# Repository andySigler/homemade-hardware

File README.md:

# Homemade Hardware

This repository holds supporting materials for the NYU-ITP graduate course [Homemade Hardware](http://www.homemadehardware.com)

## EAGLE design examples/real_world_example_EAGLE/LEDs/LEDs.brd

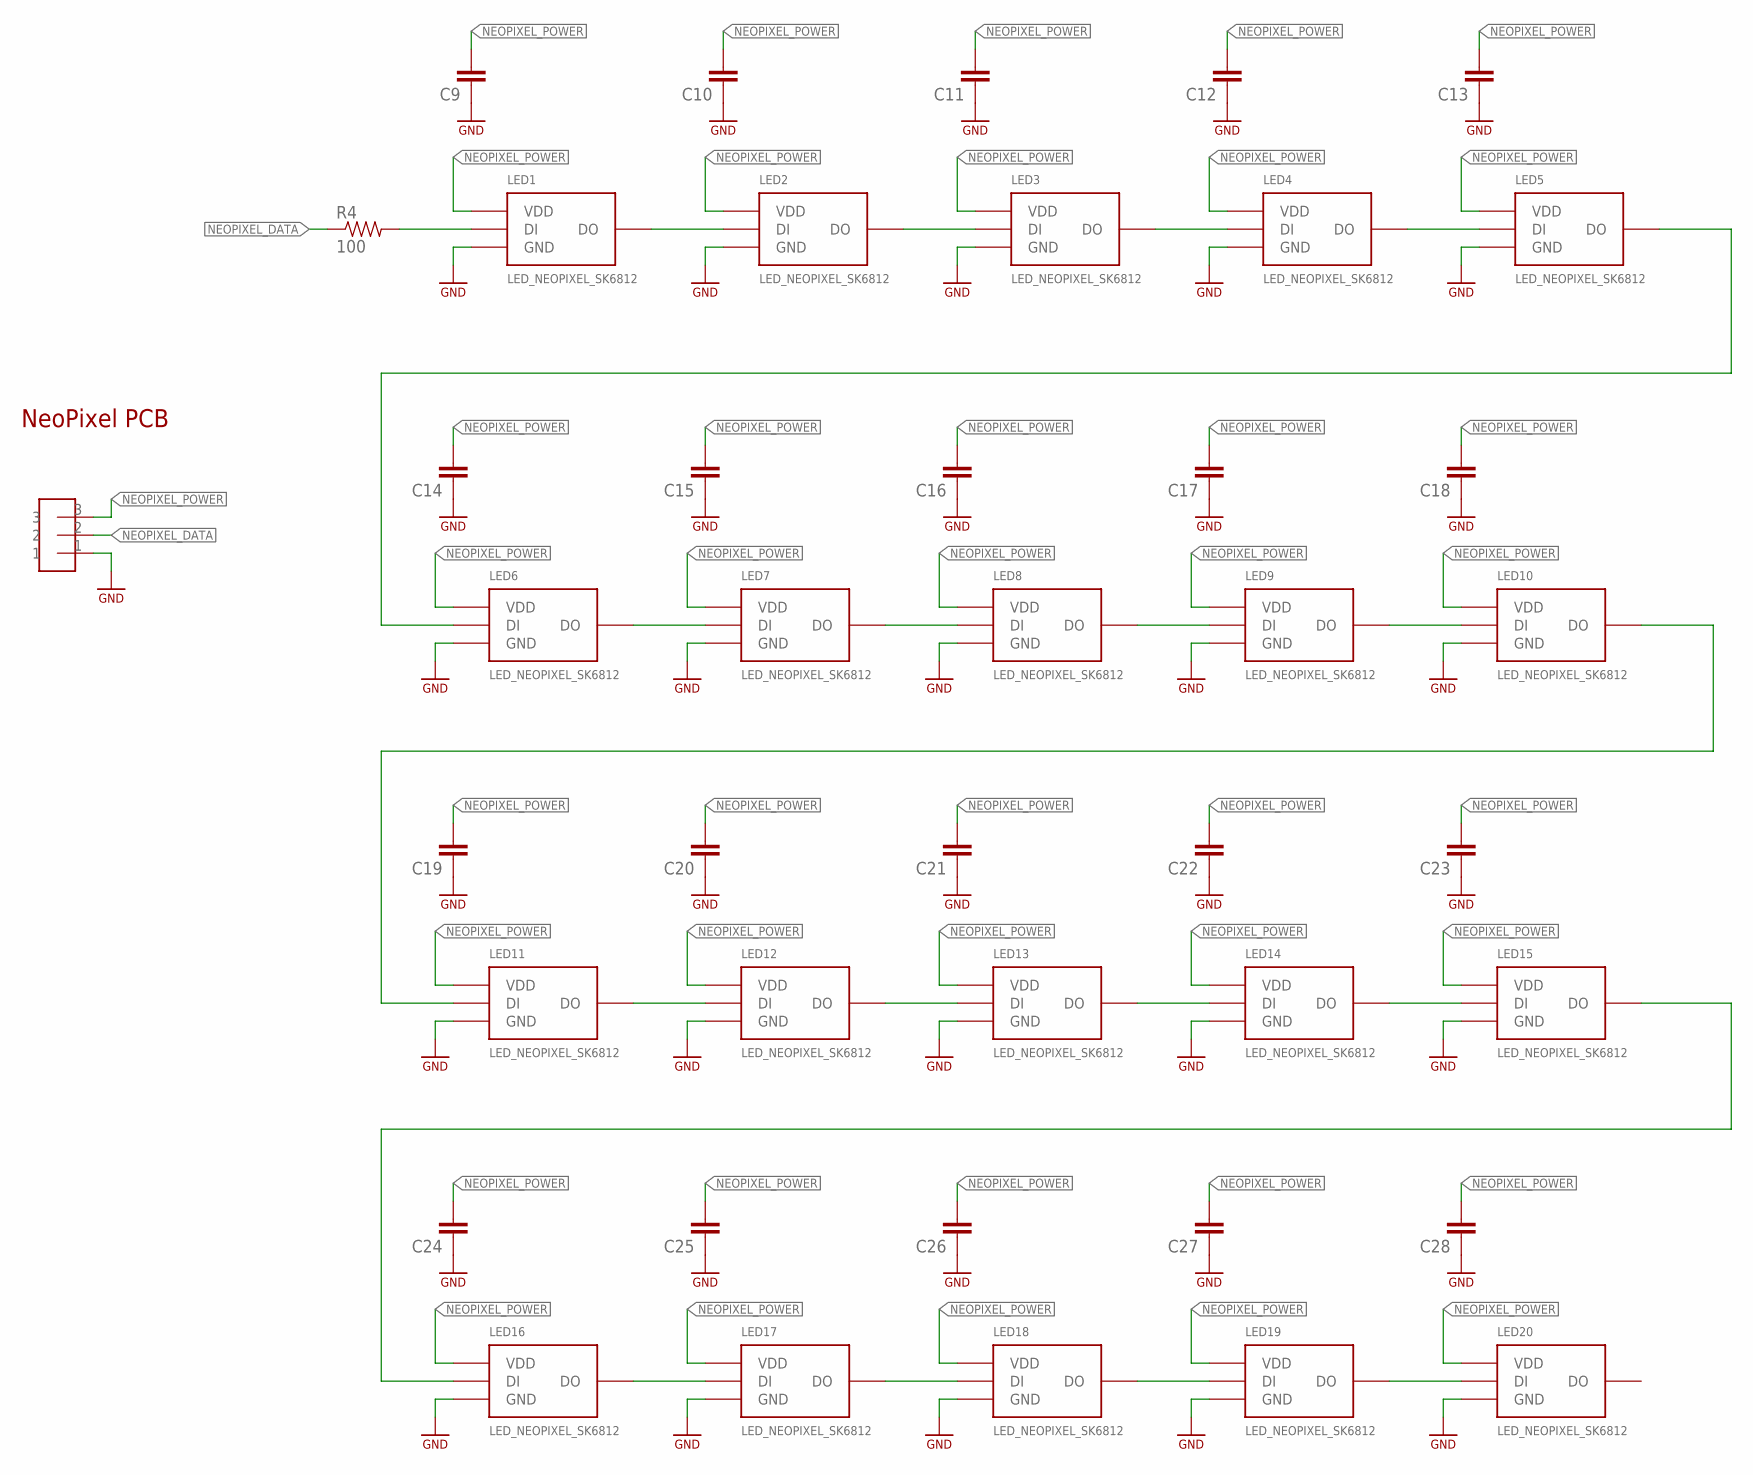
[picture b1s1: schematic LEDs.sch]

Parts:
C9, C10, C11, C12, C13, C14, C15, C16, C17, C18, C19, C20, C21, C22, C23, C24, C25, C26, C27, C28: COMPONENT_CAP-0805; 0805
LED1, LED2, LED3, LED4, LED5, LED6, LED7, LED8, LED9, LED10, LED11, LED12, LED13, LED14, LED15, LED16, LED17, LED18, LED19, LED20: LED_NEOPIXEL_SK6812; SK6812
R4: 100; 0805
U$2: HEADER-3-HORIZONTAL

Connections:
GND: C9.1, C10.1, C11.1, C12.1, C13.1, C14.1, C15.1, C16.1, C17.1, C18.1, C19.1, C20.1, C21.1, C22.1, C23.1, C24.1, C25.1, C26.1, C27.1, C28.1, LED1.3-GND (GND), LED2.3-GND (GND), LED3.3-GND (GND), LED4.3-GND (GND), LED5.3-GND (GND), LED6.3-GND (GND), LED7.3-GND (GND), LED8.3-GND (GND), LED9.3-GND (GND), LED10.3-GND (GND), LED11.3-GND (GND), LED12.3-GND (GND), LED13.3-GND (GND), LED14.3-GND (GND), LED15.3-GND (GND), LED16.3-GND (GND), LED17.3-GND (GND), LED18.3-GND (GND), LED19.3-GND (GND), LED20.3-GND (GND), U$2.1
unnamed: LED1.4-DIN (DI), R4.2
unnamed: LED1.2-DOUT (DO), LED2.4-DIN (DI)
unnamed: LED2.2-DOUT (DO), LED3.4-DIN (DI)
unnamed: LED3.2-DOUT (DO), LED4.4-DIN (DI)
unnamed: LED4.2-DOUT (DO), LED5.4-DIN (DI)
unnamed: LED5.2-DOUT (DO), LED6.4-DIN (DI)
unnamed: LED6.2-DOUT (DO), LED7.4-DIN (DI)
unnamed: LED7.2-DOUT (DO), LED8.4-DIN (DI)
unnamed: LED8.2-DOUT (DO), LED9.4-DIN (DI)
unnamed: LED9.2-DOUT (DO), LED10.4-DIN (DI)
unnamed: LED10.2-DOUT (DO), LED11.4-DIN (DI)
unnamed: LED11.2-DOUT (DO), LED12.4-DIN (DI)
unnamed: LED12.2-DOUT (DO), LED13.4-DIN (DI)
unnamed: LED13.2-DOUT (DO), LED14.4-DIN (DI)
unnamed: LED14.2-DOUT (DO), LED15.4-DIN (DI)
unnamed: LED15.2-DOUT (DO), LED16.4-DIN (DI)
unnamed: LED16.2-DOUT (DO), LED17.4-DIN (DI)
unnamed: LED17.2-DOUT (DO), LED18.4-DIN (DI)
unnamed: LED18.2-DOUT (DO), LED19.4-DIN (DI)
unnamed: LED19.2-DOUT (DO), LED20.4-DIN (DI)
NEOPIXEL_DATA: R4.1, U$2.2
NEOPIXEL_POWER: C9.2, C10.2, C11.2, C12.2, C13.2, C14.2, C15.2, C16.2, C17.2, C18.2, C19.2, C20.2, C21.2, C22.2, C23.2, C24.2, C25.2, C26.2, C27.2, C28.2, LED1.1-VDD (VDD), LED2.1-VDD (VDD), LED3.1-VDD (VDD), LED4.1-VDD (VDD), LED5.1-VDD (VDD), LED6.1-VDD (VDD), LED7.1-VDD (VDD), LED8.1-VDD (VDD), LED9.1-VDD (VDD), LED10.1-VDD (VDD), LED11.1-VDD (VDD), LED12.1-VDD (VDD), LED13.1-VDD (VDD), LED14.1-VDD (VDD), LED15.1-VDD (VDD), LED16.1-VDD (VDD), LED17.1-VDD (VDD), LED18.1-VDD (VDD), LED19.1-VDD (VDD), LED20.1-VDD (VDD), U$2.3

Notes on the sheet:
NeoPixel PCB

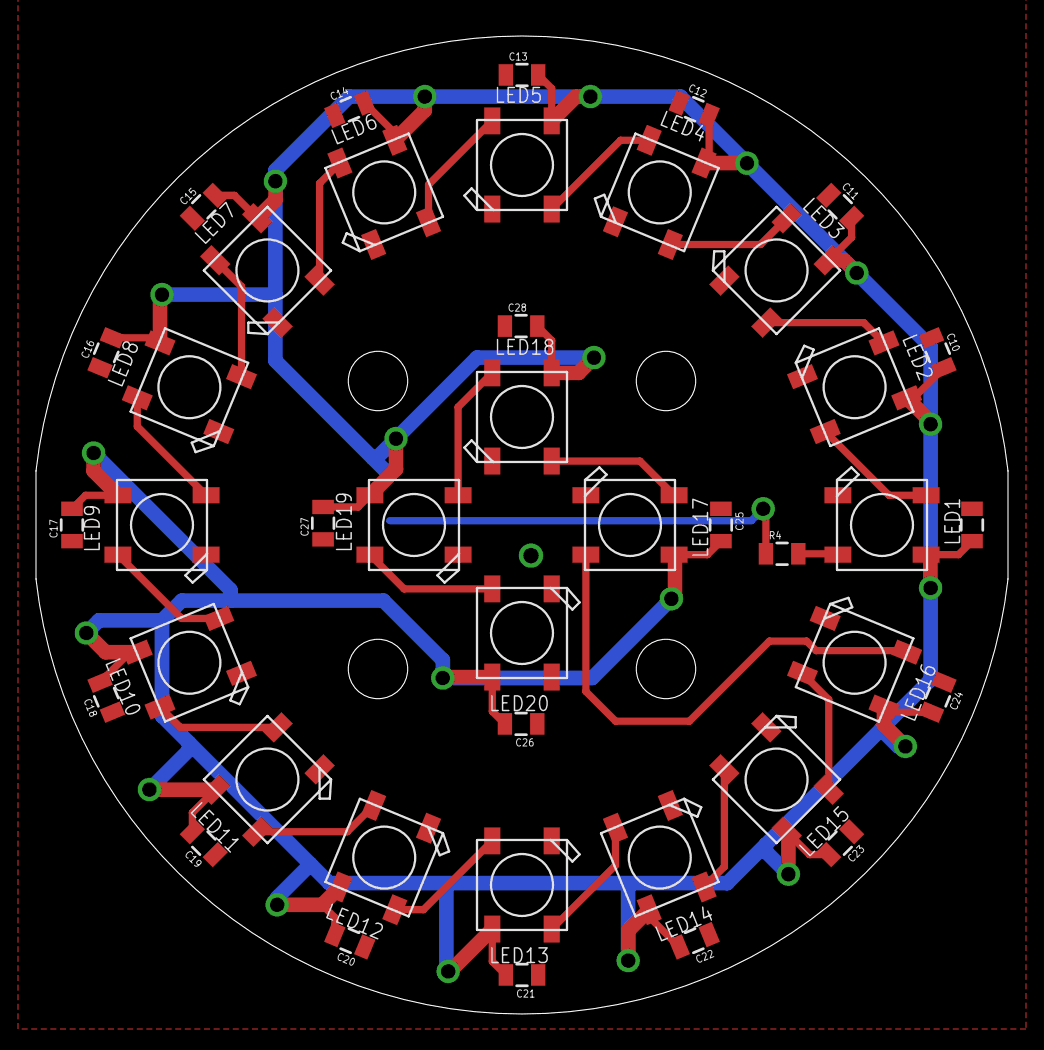
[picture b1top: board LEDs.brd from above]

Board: 2 copper layers, 54.0 x 54.3 mm, 42 parts (1 on the bottom side), 23 nets.

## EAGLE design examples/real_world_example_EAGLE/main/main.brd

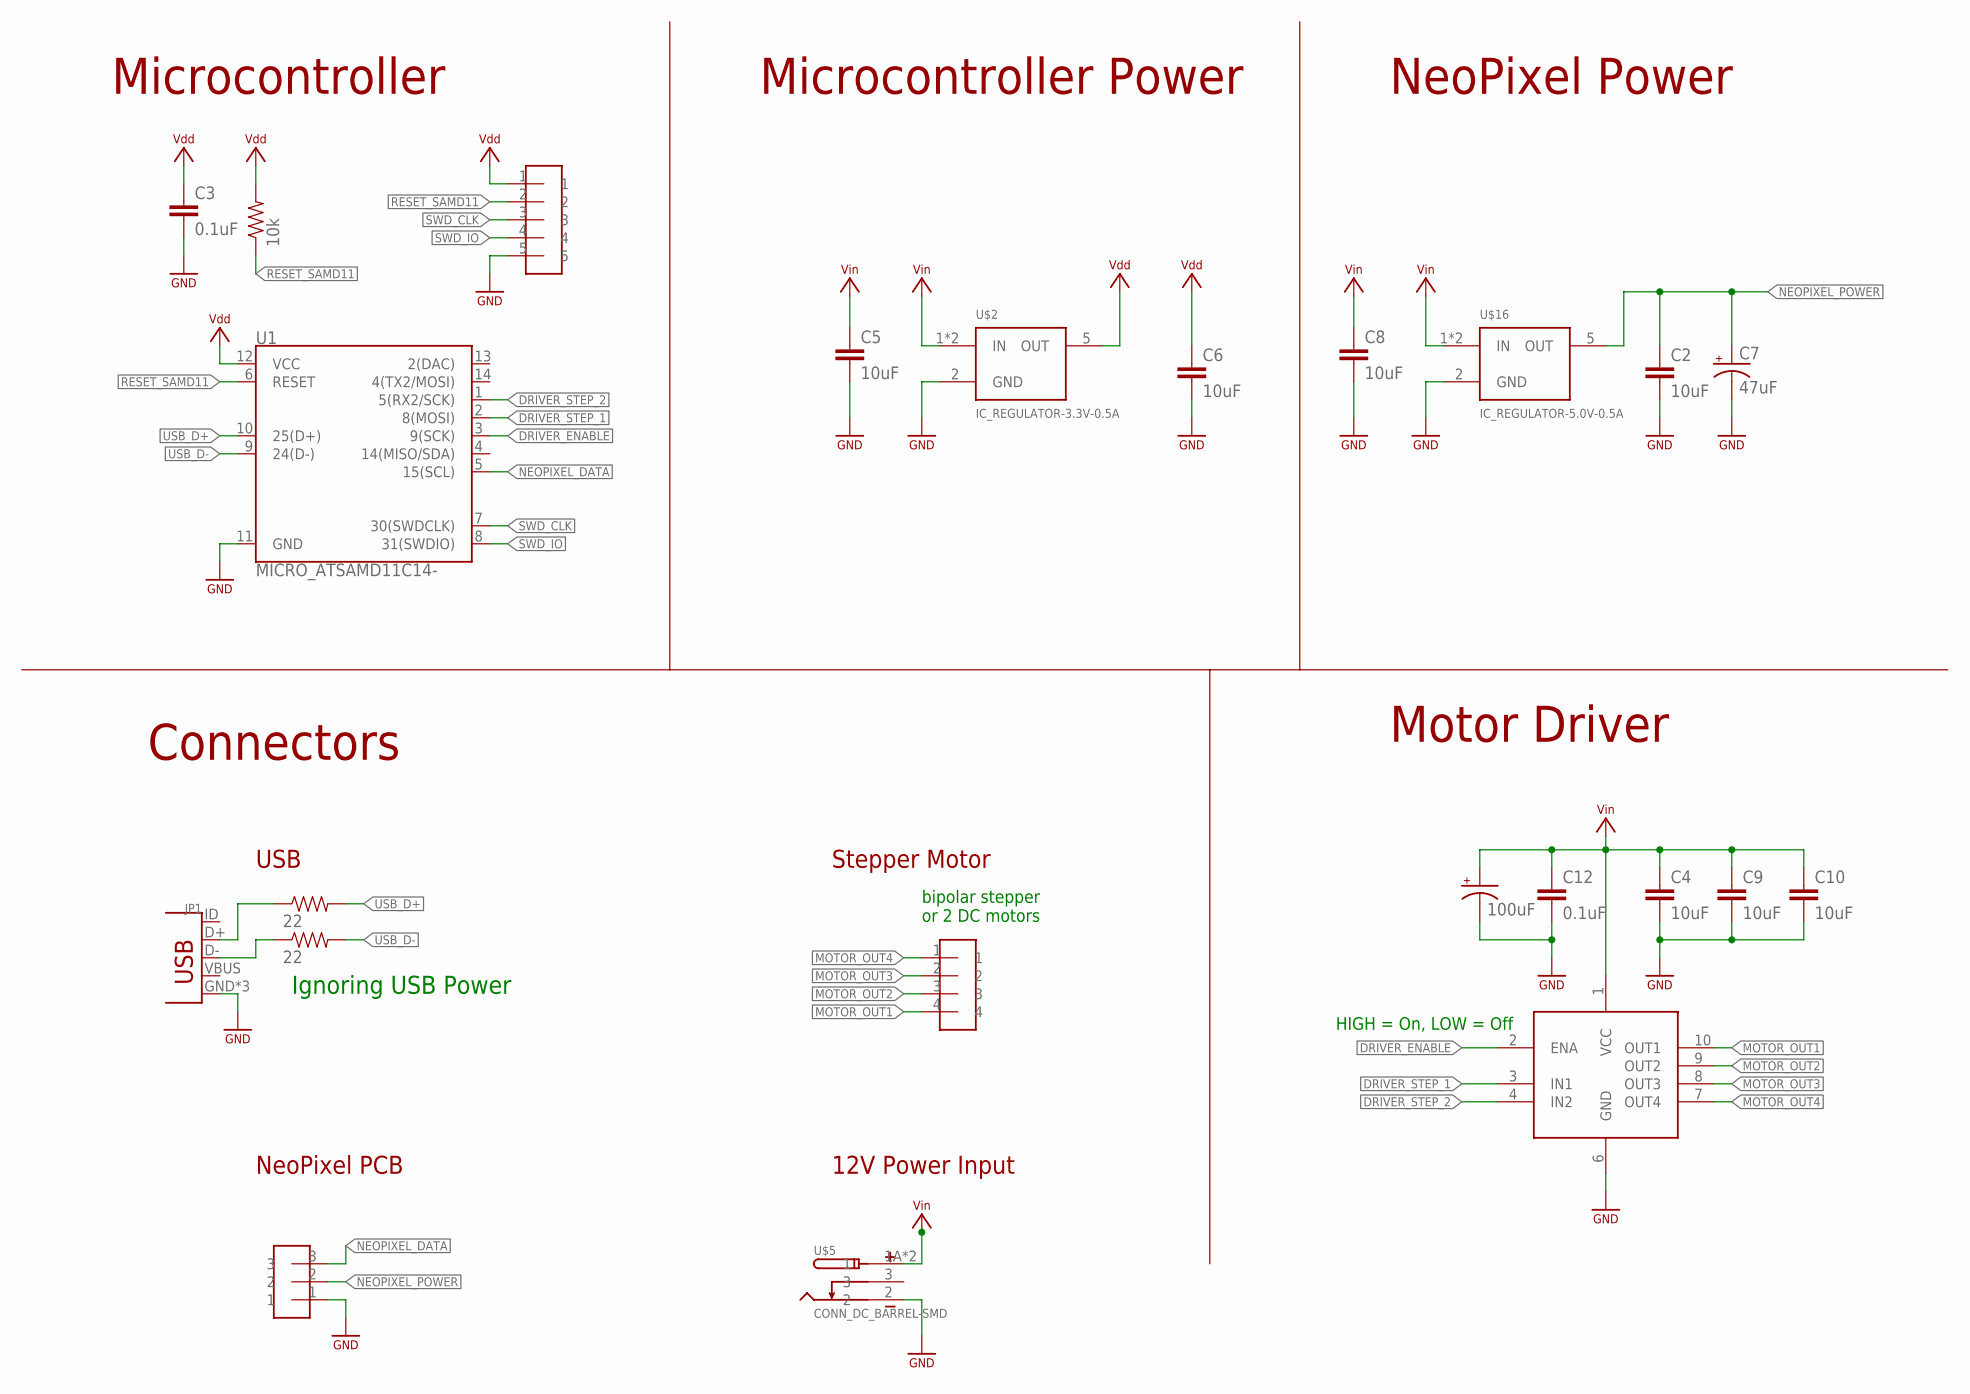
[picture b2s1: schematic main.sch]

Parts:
C1: 100uF; CAP_RADIAL_CAN_8MM
C2, C4, C5, C6, C8, C9, C10: 10uF; 0805
C3, C12: 0.1uF; 0805
C7: 47uF; CAP_RADIAL_CAN_6.3MM
JP1: CONN_USB-10118192-0001LF; USB-MICRO-FEMALE
R1: 10k; 0805
R2, R3: 22; 0805
U1: MICRO_ATSAMD11C14-; SOIC14
U$1: HEADER-4-HORIZONTAL
U$2: IC_REGULATOR-3.3V-0.5A; SOT23-5
U$3: IC_H_BRIDGE_LV8549MC; SOIC10
U$5: CONN_DC_BARREL-SMD; 694106106102
U$10: HEADER-5-TESTPOINT; TESTPOINT-5
U$16: IC_REGULATOR-5.0V-0.5A; SOT23-5
U$17: HEADER-3-HORIZONTAL

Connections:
DRIVER_ENABLE: U1.3 (9(SCK)), U$3.2 (ENA)
DRIVER_STEP_1: U1.2 (8(MOSI)), U$3.3 (IN1)
DRIVER_STEP_2: U1.1 (5(RX2/SCK)), U$3.4 (IN2)
GND: C1.-, C2.2, C3.2, C4.2, C5.2, C6.2, C7.-, C8.2, C9.2, C10.2, C12.2, JP1.GND, JP1.MT1 (GND), JP1.MT2 (GND), U1.11 (GND), U$2.2 (GND), U$3.6 (GND), U$5.2, U$10.5, U$16.2 (GND), U$17.1
MOTOR_OUT1: U$1.4, U$3.10 (OUT1)
MOTOR_OUT2: U$1.3, U$3.9 (OUT2)
MOTOR_OUT3: U$1.2, U$3.8 (OUT3)
MOTOR_OUT4: U$1.1, U$3.7 (OUT4)
unnamed: JP1.D+, R2.1
unnamed: JP1.D-, R3.1
NEOPIXEL_DATA: U1.5 (15(SCL)), U$17.3
NEOPIXEL_POWER: C2.1, C7.+, U$16.5 (OUT), U$17.2
RESET_SAMD11: R1.1, U1.6 (RESET), U$10.2
SWD_CLK: U1.7 (30(SWDCLK)), U$10.3
SWD_IO: U1.8 (31(SWDIO)), U$10.4
USB_D+: R2.2, U1.10 (25(D+))
USB_D-: R3.2, U1.9 (24(D-))
VDD: C3.1, C6.1, R1.2, U1.12 (VCC), U$2.5 (OUT), U$10.1
VIN: C1.+, C4.1, C5.1, C8.1, C9.1, C10.1, C12.1, U$2.1 (IN), U$2.3 (IN), U$3.1 (VCC), U$5.1A (1), U$5.1B (1), U$16.1 (IN), U$16.3 (IN)

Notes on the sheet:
HIGH = On, LOW = Off
bipolar stepper or 2 DC motors
Microcontroller
Connectors
Motor Driver
Microcontroller Power
USB
Stepper Motor
12V Power Input
NeoPixel PCB
NeoPixel Power
Ignoring USB Power

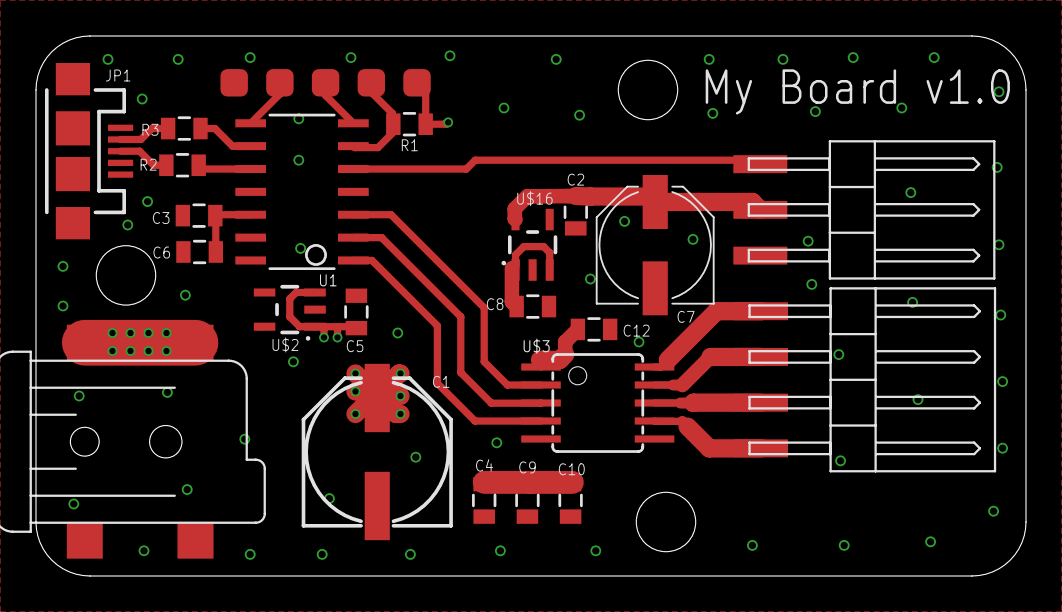
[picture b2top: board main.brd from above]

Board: 4 copper layers, 55.0 x 30.0 mm, 23 parts (0 on the bottom side), 19 nets.

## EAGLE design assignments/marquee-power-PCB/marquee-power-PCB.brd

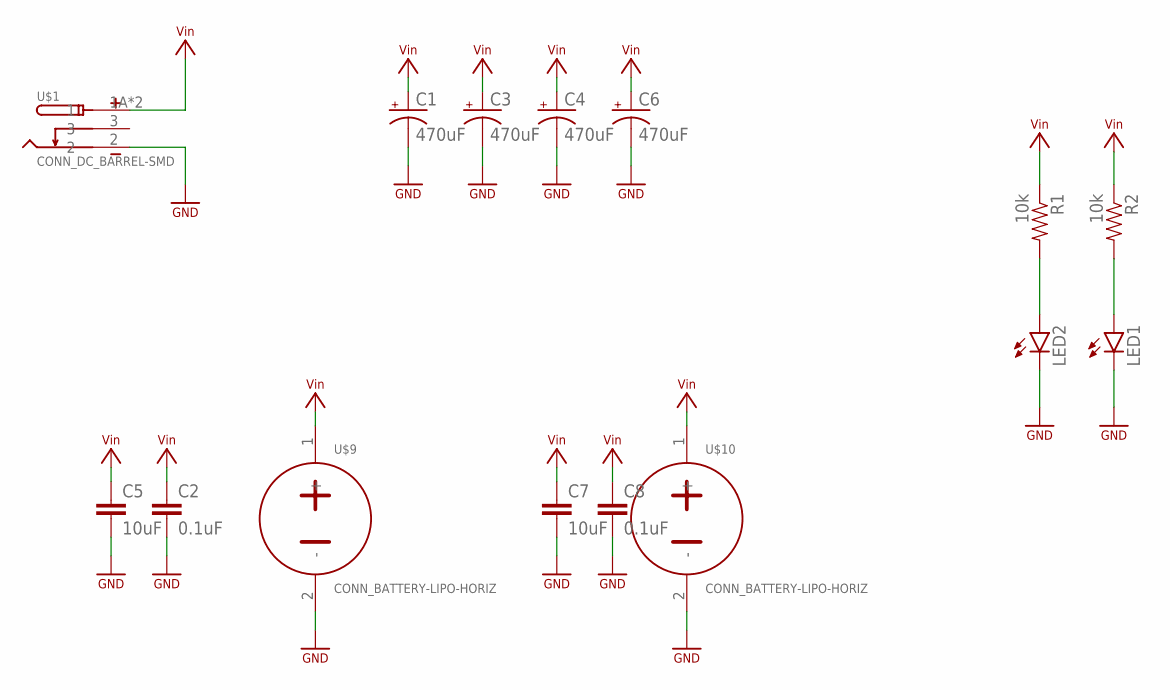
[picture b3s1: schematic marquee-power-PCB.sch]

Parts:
C1, C3, C4, C6: 470uF; CAP_RADIAL_CAN_10MM
C2, C8: 0.1uF; 0805
C5, C7: 10uF; 0805
LED1, LED2: LED-0805; CHIP-LED0805
R1, R2: 10k; 0805
U$1: CONN_DC_BARREL-SMD; 694106106102
U$9, U$10: CONN_BATTERY-LIPO-HORIZ; JST-PH-2-SMT-RA

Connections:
GND: C1.-, C2.2, C3.-, C4.-, C5.2, C6.-, C7.2, C8.2, LED1.C, LED2.C, U$1.2, U$9.2 (-), U$10.2 (-)
unnamed: LED2.A, R1.2
unnamed: LED1.A, R2.2
VIN: C1.+, C2.1, C3.+, C4.+, C5.1, C6.+, C7.1, C8.1, R1.1, R2.1, U$1.1A (1), U$1.1B (1), U$9.1 (+), U$10.1 (+)

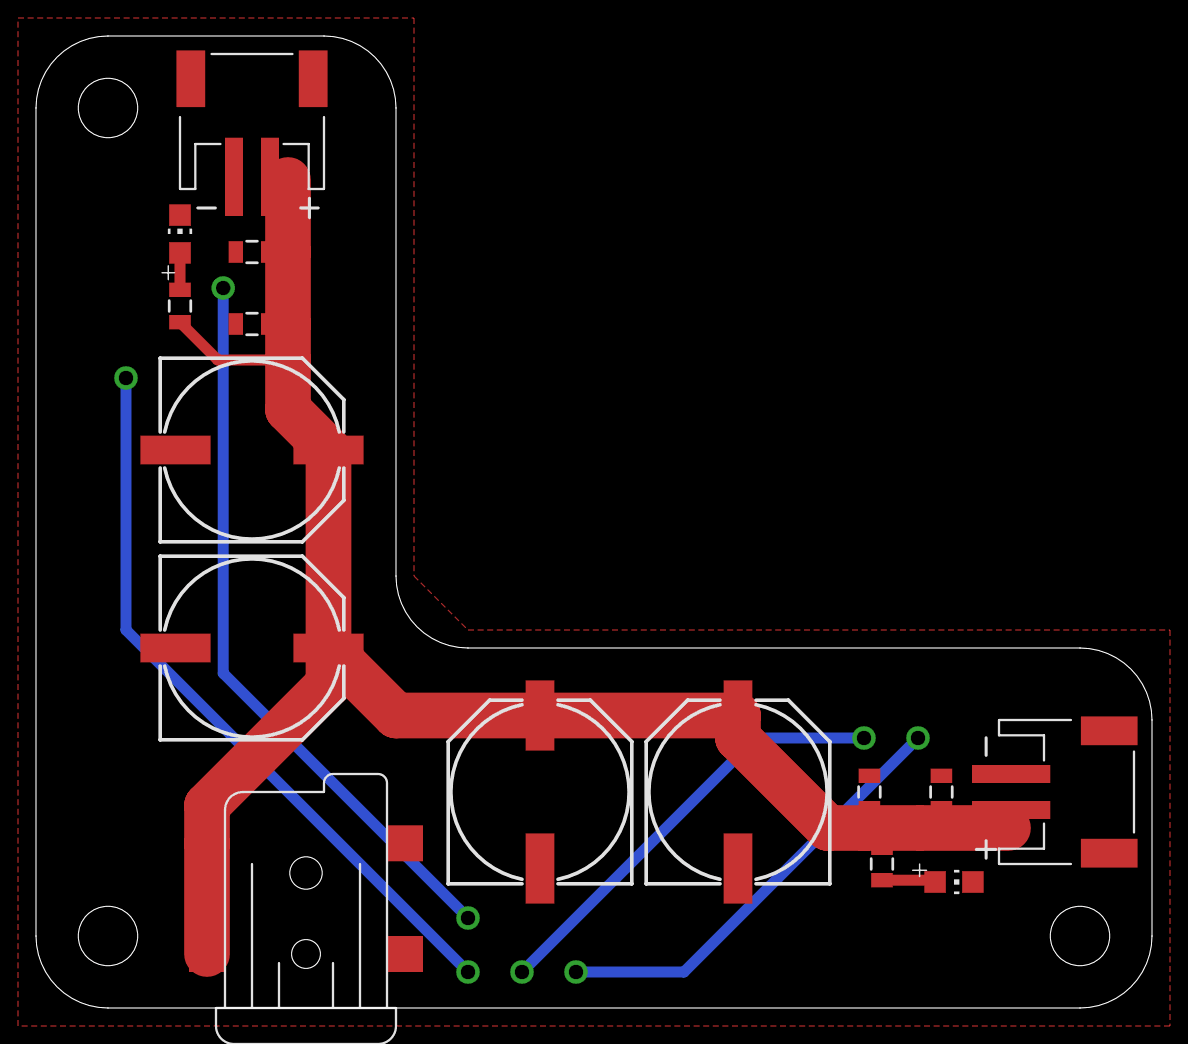
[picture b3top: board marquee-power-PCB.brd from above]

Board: 2 copper layers, 62.0 x 54.0 mm, 15 parts (0 on the bottom side), 4 nets.

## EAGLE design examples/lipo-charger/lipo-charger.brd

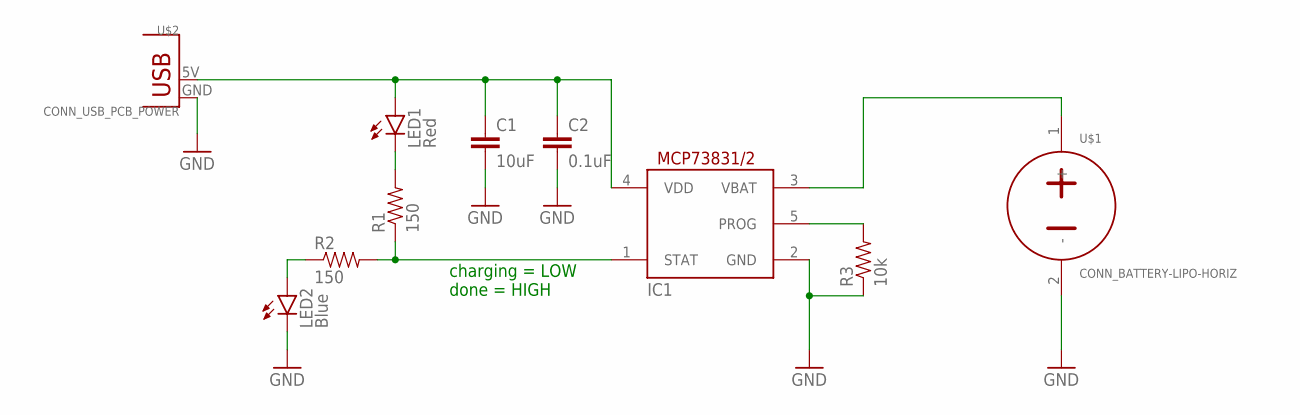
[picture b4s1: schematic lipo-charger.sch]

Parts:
C1: 10uF; 0805
C2: 0.1uF; 0805
IC1: IC_LIPO_CHARGER; SOT23-5
LED1: Red; CHIP-LED0805
LED2: Blue; CHIP-LED0805
R1, R2: 150; 0805
R3: 10k; 0805
U$1: CONN_BATTERY-LIPO-HORIZ; JST-PH-2-SMT-RA
U$2: CONN_USB_PCB_POWER; USB-PCB-POWER

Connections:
5V: C1.1, C2.1, IC1.4 (VDD), LED1.A, U$2.5V (VBUS)
BATTERY: IC1.3 (VBAT), U$1.1 (+)
CURRENT-CONTROL: IC1.5 (PROG), R3.2
GND: C1.2, C2.2, IC1.2 (GND), LED2.C, R3.1, U$1.2 (-), U$2.GND
unnamed: LED1.C, R1.2
unnamed: LED2.A, R2.1
STATUS: IC1.1 (STAT), R1.1, R2.2

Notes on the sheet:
charging = LOW done = HIGH

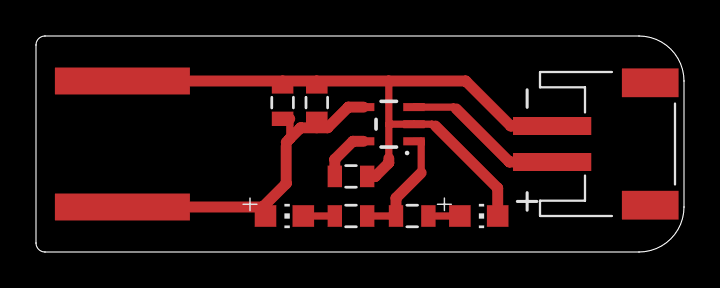
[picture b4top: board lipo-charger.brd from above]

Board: 2 copper layers, 36.0 x 12.0 mm, 10 parts (0 on the bottom side), 7 nets.

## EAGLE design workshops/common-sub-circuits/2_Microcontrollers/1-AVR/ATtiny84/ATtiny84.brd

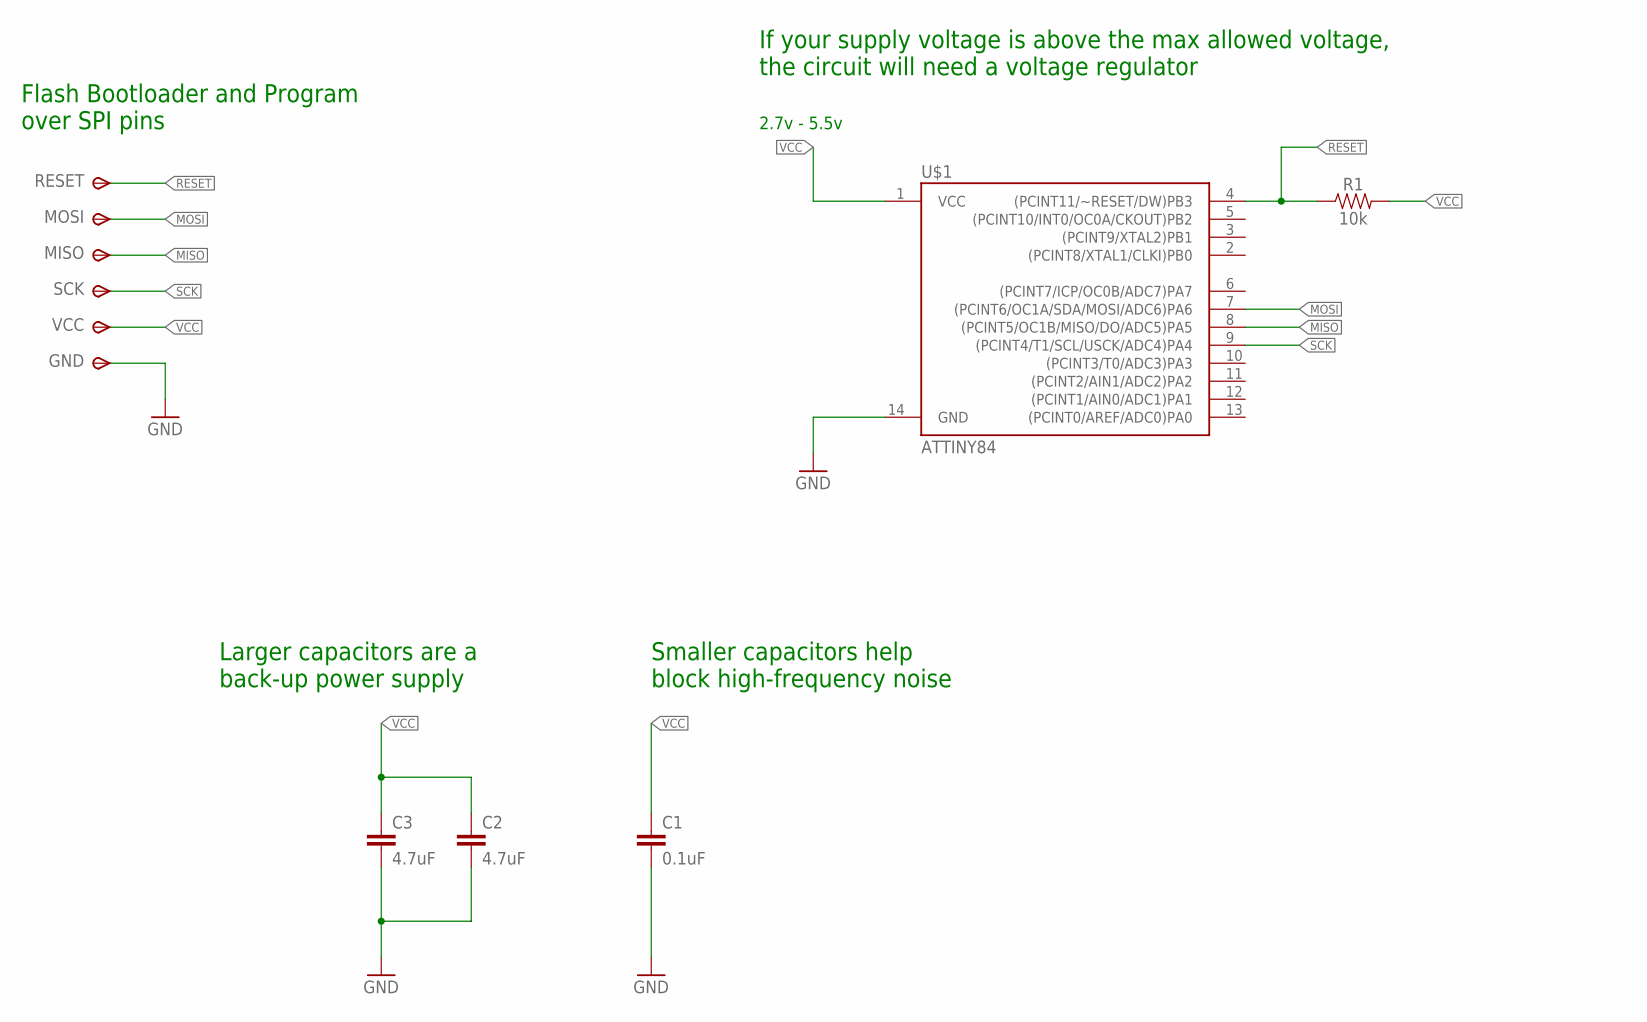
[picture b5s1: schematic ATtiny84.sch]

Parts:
C1: 0.1uF; 0603
C2, C3: 4.7uF; 0603
GND: TPSTP14SQ; TP14SQ
MISO: TPSTP14SQ; TP14SQ
MOSI: TPSTP14SQ; TP14SQ
R1: 10k; 0603
RESET: TPSTP14SQ; TP14SQ
SCK: TPSTP14SQ; TP14SQ
U$1: ATTINY84; SO14
VCC: TPSTP14SQ; TP14SQ

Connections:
GND: C1.2, C2.2, C3.2, GND.TP, U$1.14 (GND)
MISO: MISO.TP, U$1.8 ((PCINT5/OC1B/MISO/DO/ADC5)PA5)
MOSI: MOSI.TP, U$1.7 ((PCINT6/OC1A/SDA/MOSI/ADC6)PA6)
RESET: R1.1, RESET.TP, U$1.4 ((PCINT11/~RESET/DW)PB3)
SCK: SCK.TP, U$1.9 ((PCINT4/T1/SCL/USCK/ADC4)PA4)
VCC: C1.1, C2.1, C3.1, R1.2, U$1.1 (VCC), VCC.TP

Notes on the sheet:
2.7v - 5.5v
Flash Bootloader and Program over SPI pins
If your supply voltage is above the max allowed voltage, the circuit will need a voltage regulator
Smaller capacitors help block high-frequency noise
Larger capacitors are a back-up power supply

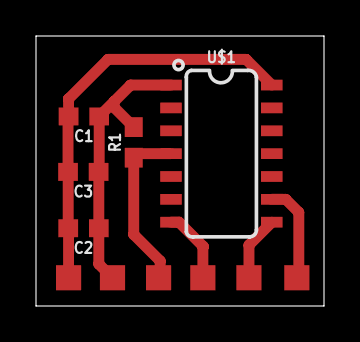
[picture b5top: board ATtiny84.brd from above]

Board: 2 copper layers, 16.0 x 15.0 mm, 11 parts (0 on the bottom side), 6 nets.

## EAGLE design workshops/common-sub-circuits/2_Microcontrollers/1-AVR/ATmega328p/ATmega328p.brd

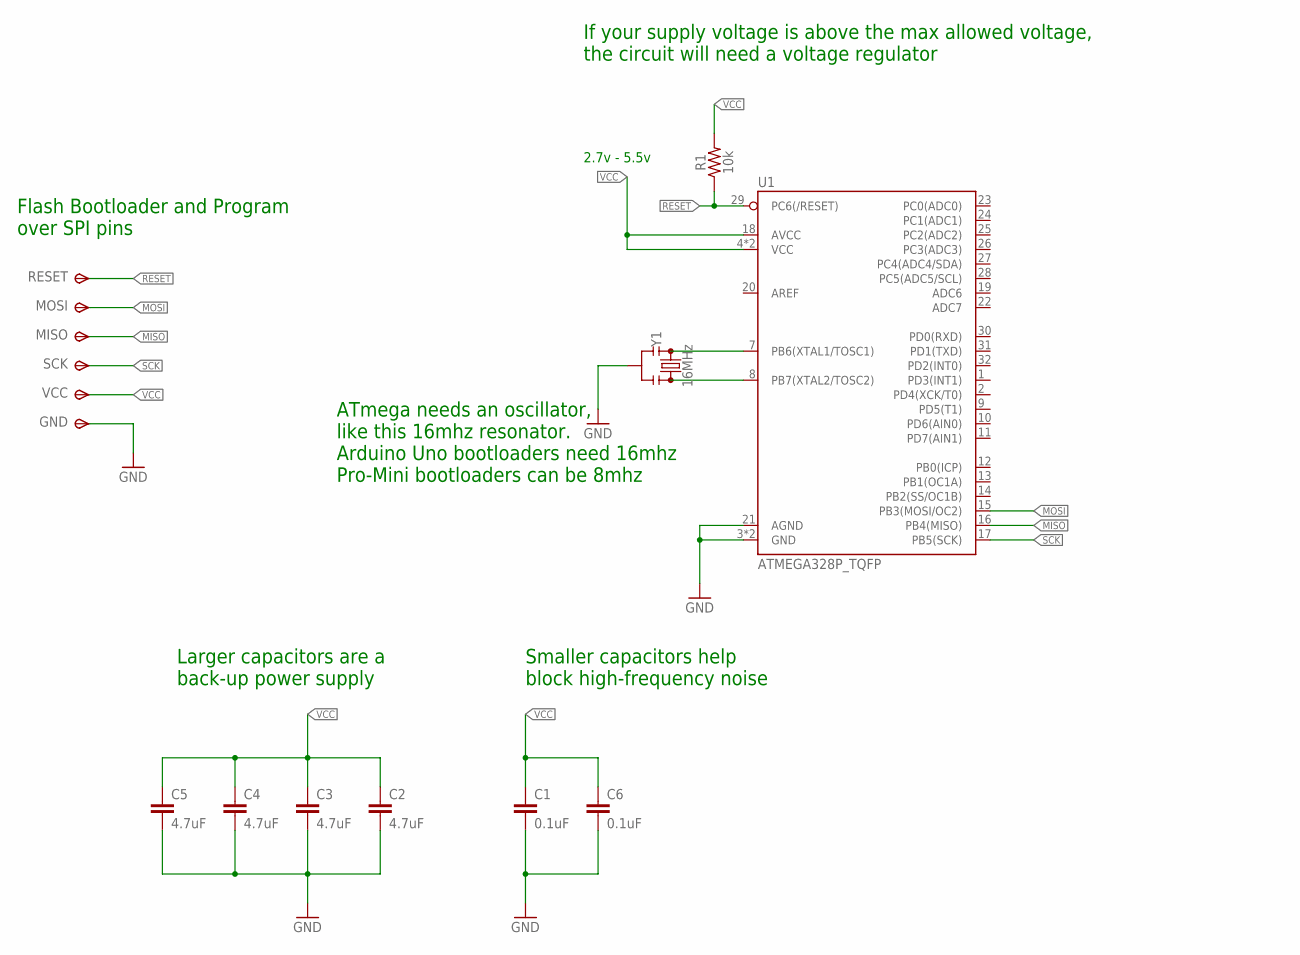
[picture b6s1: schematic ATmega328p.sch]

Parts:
C1, C6: 0.1uF; 0603
C2, C3, C4, C5: 4.7uF; 0603
GND: TPSTP14SQ; TP14SQ
MISO: TPSTP14SQ; TP14SQ
MOSI: TPSTP14SQ; TP14SQ
R1: 10k; 0603
RESET: TPSTP14SQ; TP14SQ
SCK: TPSTP14SQ; TP14SQ
U1: ATMEGA328P_TQFP; TQFP32-08
VCC: TPSTP14SQ; TP14SQ
Y1: 16MHz; RESONATOR-SMD-3.2X1.3

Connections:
GND: C1.2, C2.2, C3.2, C4.2, C5.2, C6.2, GND.TP, U1.3 (GND), U1.5 (GND), U1.21 (AGND), Y1.2
MISO: MISO.TP, U1.16 (PB4(MISO))
MOSI: MOSI.TP, U1.15 (PB3(MOSI/OC2))
unnamed: U1.7 (PB6(XTAL1/TOSC1)), Y1.1
unnamed: U1.8 (PB7(XTAL2/TOSC2)), Y1.3
RESET: R1.1, RESET.TP, U1.29 (PC6(/RESET))
SCK: SCK.TP, U1.17 (PB5(SCK))
VCC: C1.1, C2.1, C3.1, C4.1, C5.1, C6.1, R1.2, U1.4 (VCC), U1.6 (VCC), U1.18 (AVCC), VCC.TP

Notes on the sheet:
2.7v - 5.5v
Flash Bootloader and Program over SPI pins
If your supply voltage is above the max allowed voltage, the circuit will need a voltage regulator
Smaller capacitors help block high-frequency noise
Larger capacitors are a back-up power supply
ATmega needs an oscillator, like this 16mhz resonator. Arduino Uno bootloaders need 16mhz Pro-Mini bootloaders can be 8mhz

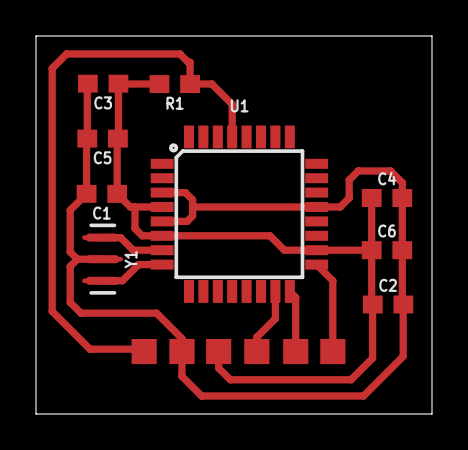
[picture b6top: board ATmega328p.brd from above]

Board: 2 copper layers, 22.0 x 21.0 mm, 15 parts (0 on the bottom side), 8 nets.

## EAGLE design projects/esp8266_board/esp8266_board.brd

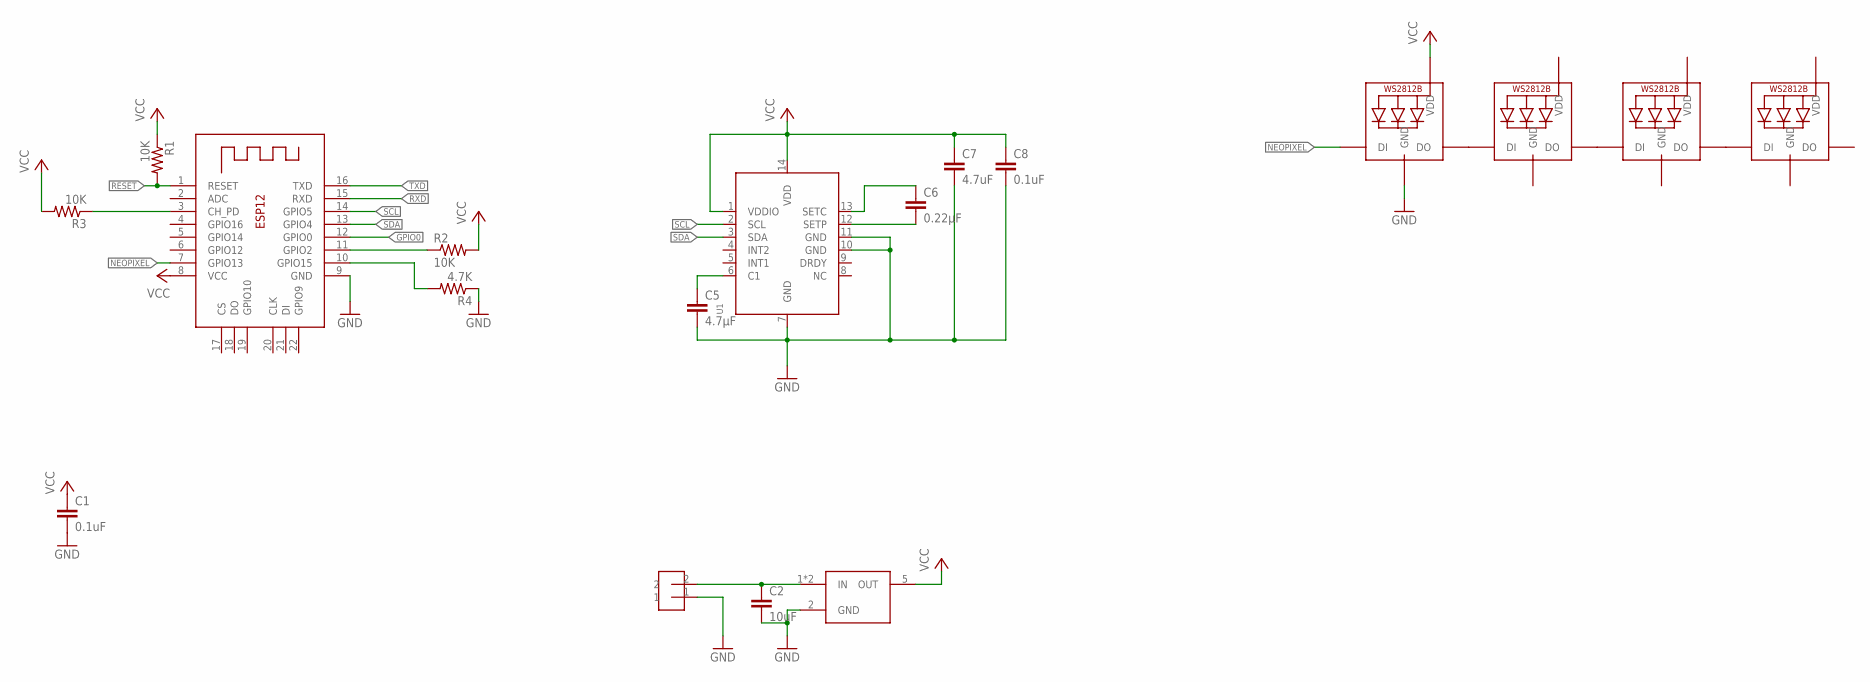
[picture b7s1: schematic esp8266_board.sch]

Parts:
C1, C8: 0.1uF; 0603-CAP
C2: 10uF; 0603-CAP
C5: 4.7µF; 0603-CAP
C6: 0.22µF; 0603-CAP
C7: 4.7uF; 0603-CAP
LED1, LED2, LED3, LED4: NEOPIXEL_SK6812; SK6812
R1, R2, R3: 10K; 0603-RES
R4: 4.7K; 0603-RES
U1: LSM303DLHC; LGA14
U$1: REGULATOR3.3V-0.5A-MIC5219; SOT23-5
U$2: HEADER-2-TESTPOINT; TESTPOINT-2
X2: ESP-12E

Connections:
GND: C1.2, C2.2, C5.2, C7.2, C8.2, LED1.3-GND (GND), LED2.3-GND (GND), LED3.3-GND (GND), LED4.3-GND (GND), R4.1, U1.7 (GND), U1.10 (GND), U1.11 (GND), U$1.2 (GND), U$2.1, X2.9 (GND)
GPIO0: X2.12 (GPIO0)
unnamed: R4.2, X2.10 (GPIO15)
unnamed: R3.1, X2.3 (CH_PD)
unnamed: C5.1, U1.6 (C1)
unnamed: C6.2, U1.12 (SETP)
unnamed: C6.1, U1.13 (SETC)
unnamed: R2.1, X2.11 (GPIO2)
unnamed: LED1.2-DOUT (DO), LED2.4-DIN (DI)
unnamed: LED2.2-DOUT (DO), LED3.4-DIN (DI)
unnamed: LED3.2-DOUT (DO), LED4.4-DIN (DI)
NEOPIXEL: LED1.4-DIN (DI), X2.7 (GPIO13)
RESET: R1.2, X2.1 (RESET)
RXD: X2.15 (RXD)
SCL: U1.2 (SCL), X2.14 (GPIO5)
SDA: U1.3 (SDA), X2.13 (GPIO4)
TXD: X2.16 (TXD)
VCC: C1.1, C7.1, C8.1, LED1.1-VDD (VDD), R1.1, R2.2, R3.2, U1.1 (VDDIO), U1.14 (VDD), U$1.5 (OUT), X2.8 (VCC)
VDD: LED2.1-VDD (VDD), LED3.1-VDD (VDD), LED4.1-VDD (VDD)
VIN: C2.1, U$1.1 (IN), U$1.3 (IN), U$2.2

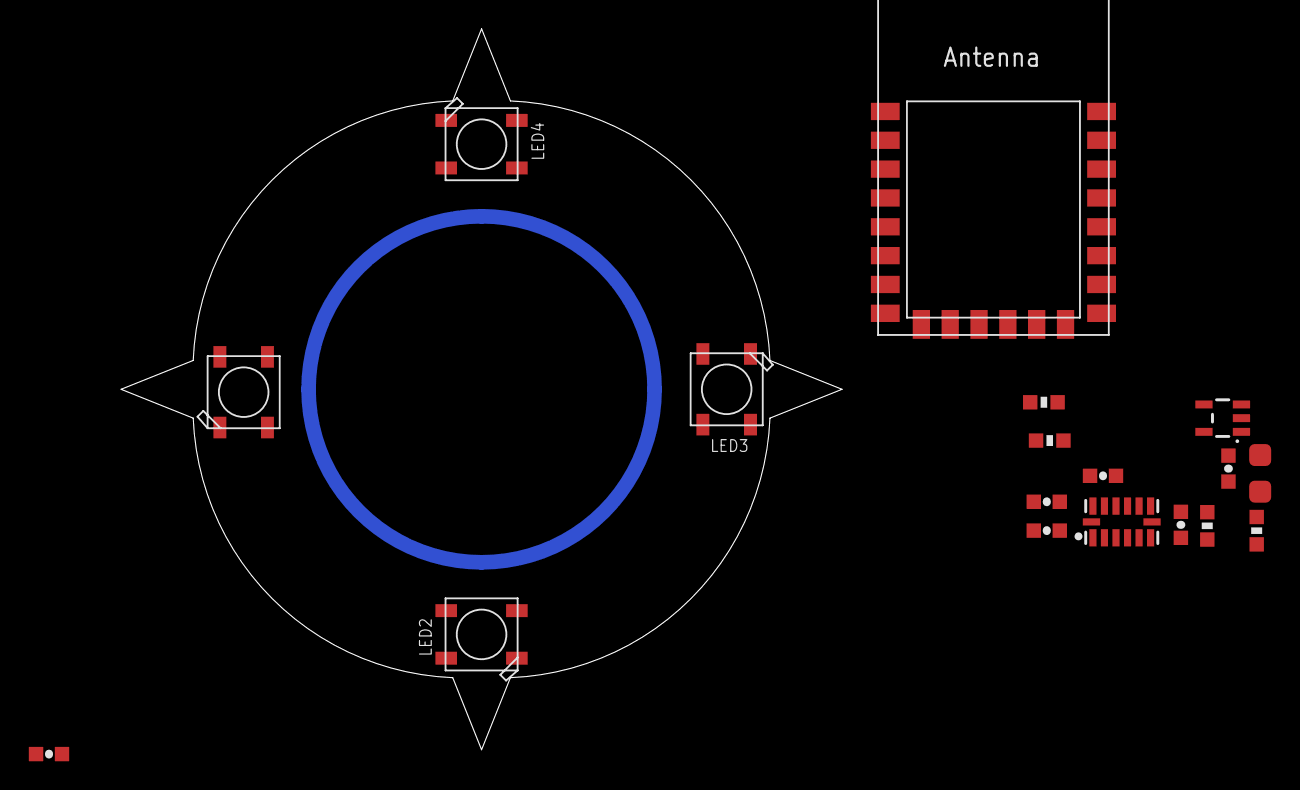
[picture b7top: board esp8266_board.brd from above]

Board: 2 copper layers, 50.0 x 50.0 mm, 18 parts (0 on the bottom side), 17 nets.

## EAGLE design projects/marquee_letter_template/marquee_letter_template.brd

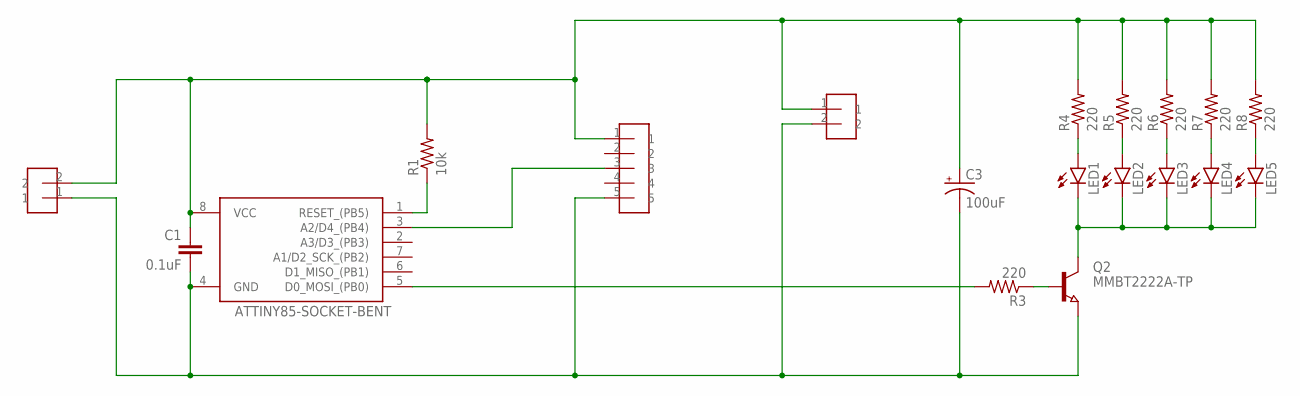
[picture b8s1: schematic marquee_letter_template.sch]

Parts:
C1: 0.1uF; 0805
C3: 100uF; PANASONIC_D
LED1, LED2, LED3, LED4, LED5: LED0603; LED-0603
POTENTIOMETER: HEADER-5
Q2: MMBT2222A-TP; SOT23
R1: 10k; 0805
R3: 220; 0805
R4, R5, R6, R7, R8: 220; 0603-RES
U$1: ATTINY85-SOCKET-BENT; SOCKET-8PIN-BENT
U$2, U$3: HEADER-2

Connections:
5V: C1.1, C3.+, POTENTIOMETER.1, R1.2, R4.2, R5.2, R6.2, R7.2, R8.2, U$1.8 (VCC), U$2.2, U$3.1
GND: C1.2, C3.-, POTENTIOMETER.5, Q2.2 (E), U$1.4 (GND), U$2.1, U$3.2
unnamed: LED1.A, R4.1
unnamed: R3.2, U$1.5 (D0_MOSI_(PB0))
unnamed: LED1.C, LED2.C, LED3.C, LED4.C, LED5.C, Q2.3 (C)
unnamed: Q2.1 (B), R3.1
unnamed: LED2.A, R5.1
unnamed: LED3.A, R6.1
unnamed: LED4.A, R7.1
unnamed: LED5.A, R8.1
unnamed: R1.1, U$1.1 (RESET_(PB5))
SENSOR: POTENTIOMETER.3, U$1.3 (A2/D4_(PB4))

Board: 2 copper layers, 19 parts (0 on the bottom side), 12 nets, no tracks yet.

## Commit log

2015-04-09 added DIP and SMD boards
2015-04-10 finished routing DIP board and added tool patch for 1/32
2015-04-10 nada
2015-04-14 added read me to SMD page
2015-04-14 asdf
2015-04-14 added image
2015-04-14 changed url of image
2015-04-14 added pinout image
2015-04-14 image
2015-04-14 image a litte
2015-04-15 changed image
2015-04-15 new image
2015-04-15 image smaller
2015-04-15 updated pic
2015-04-16 changed to 8MHz and Pro Mini boot loader
2015-04-16 changed readme
2015-04-16 added picture
2015-04-16 change image url
2015-06-27 much commit, so wow
2015-06-28 added combination radio board
2015-07-02 redesigned radios breakout
2015-07-02 about to cut board
2015-07-12 updated so nrf51 uses SPI instead of UART
2015-07-29 SPI combined board ready to print
2015-08-10 replaced chip antenna with pad for wire
2015-08-29 started Eagle library for ITP parts
2015-09-10 updated library, and programmer shield
2015-09-10 image links fixed
2015-09-10 removed explanation of ATmega329 (non-p) boards
2015-09-10 updated parts list
2015-09-17 added bare-bones ATmega328 board for routing in class
2015-09-22 updated radio with better regulator
2015-09-24 added ATtiny board sample for milling in class 4
2015-10-08 added lipo charger and class_6 folder
2015-10-12 updated LiPo charger circuit for class 6
2016-06-22 added tv-b-gone board; updated .gitignore of eagle backup files
2016-07-10 board ready for printing
2016-08-17 presenter-b-gone ready to order
2016-08-27 about to populate panels at ITP
2016-08-27 added tCream image
2016-08-27 added tCream images
2017-03-09 prep lipo board for class 6
2019-03-20 re-organizes; updates eagle library
2019-04-01 cleanup
2019-04-01 removes files
2019-04-01 adds readme
2019-04-01 adds board design intro files; increases attiny85 bent leg size
2019-04-01 gives names to connections in jig pcb
2019-04-02 modifies bantam DRU files for better ground pours and thicker traces
2019-04-02 adds parts image to help population
2019-04-02 remove colon
2019-04-02 remvoes colon from schematic
2019-04-02 fix error in lipo-charger LED polarity image
2019-04-09 adds NPN transistor to library
2019-04-09 increases space between pads on 0603 capacitor
2019-04-09 adds image of H letter with assembled PCB
2019-04-09 add gif showing H interaction
2019-04-09 create marquee letter template; adds image and gif of example board
2019-04-16 add h-bridge to library and examples
2019-04-16 adds SAMD11 and esp8266 example boards
2019-05-12 fixes H-bridge package; adds CR2032 smd holder
2019-12-26 reorganizes folder structure
2019-12-26 further aligns library with SMD parts for 2020
2019-12-26 adds more connectors
2019-12-27 adds SMD headers
2019-12-28 adds ICs to library
2019-12-29 marquee template; shrinks some footprints for marquee board
2019-12-29 cleans up footprints and symbols
2019-12-29 adds remaining recommended parts
2019-12-29 lipo board uses new parts
2019-12-30 finishes lipo pcb design
2020-01-01 adds microcontroller example schematics
2020-01-01 makes lipo image easier to read
2020-02-13 marquee template; schematic images
2020-02-14 finishes basics examples
2020-02-14 moves unfinished examples to private dir
2020-02-14 adds examples for comms, regs, and trans
2020-02-18 adds marquee power PCB
2020-03-13 update marquee power pcb
2020-03-13 simplifies ESP8266 arduino demo
2020-03-13 adds simple BLE esp32 example
2020-03-13 updates ATSAMD11C14A example
2021-02-23 syncing
2021-09-13 adds arduino anno 33 iot/ble
2021-09-13 adds real-world example from tutorial

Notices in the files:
parts and their libraries:
microbuilder: This work is placed in the public domain, and may be freely used for commercial and non-commercial work with the following conditions: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
SparkFun-Resistors: Licensing: Creative Commons ShareAlike 4.0 International - https://creativecommons.org/licenses/by-sa/4.0
